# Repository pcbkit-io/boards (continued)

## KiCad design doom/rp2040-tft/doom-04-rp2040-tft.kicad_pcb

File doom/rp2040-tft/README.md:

# 04 · rp2040-tft — the bare RP2040 with a colour screen and an SD card

Variant 02's processor without the module: the RP2040 chip with Raspberry Pi's minimal design
(12 MHz crystal, 16 MB W25Q128 QSPI flash, BOOTSEL and RESET buttons), a 1.8" colour TFT, a
microSD slot for the WAD, PWM sound through a class-D amplifier, and two 18650 Li-ion cells it
charges from its own USB-C. JLCPCB assembles everything but the display module, which plugs into
the socket it solders.

| | |
|---|---|
| Processor | RP2040 (QFN-56): 2 × **Cortex-M0+** (ARMv6-M), 133 MHz rated (rp2040-doom: 270 MHz), 264 KB SRAM, no internal flash; W25Q128JVSIQ 16 MB on the QSPI (XIP), 12 MHz crystal |
| Display | 1.8" 128 × 160 TFT, ST7735S (MSP1803), SPI0 (GPIO18 SCK, GPIO19 MOSI, GPIO17 CS, GPIO20 A0/DC, GPIO21 RESET), backlight GPIO22 |
| Storage | microSD (Hirose DM3AT) on SPI1 (GPIO10–13), card detect GPIO14 |
| Input | 8 × 6 mm tact switches: GPIO2–GPIO9 |
| Sound | GPIO15 PWM → 1 kΩ / 10 nF low-pass → PAM8403 (left channel, shutdown on GPIO16) → 8 Ω speaker on JST PH |
| Power | 2 × 18650 Li-ion in parallel (1S2P, a 2 A resettable fuse per cell) → reverse-cell P-FET (AO3401A) → DW01A + FS8205A protection; BQ24075 charger with power path from USB-C (1 A PTC + TVS on VBUS); its SYS output feeds the TLV75533 3.3 V LDO (enabled by the slide switch) and the PAM8403 |
| Programming | USB-C to the RP2040's USB (27 Ω series, USBLC6 ESD array): hold BOOT, tap RESET → the boot ROM's UF2 drive; SWD on a 3-pin header on the back |
| Board | 132 × 104 mm, **4 layers** (GND plane on In1), four M3 holes; front: display, buttons, BOOT, RESET, on/off switch, USB-C, charge LEDs, test pads; back: the RP2040 and the rest, the two 18650 holders across the top half |

<!-- STATUS -->
**Board status** (measured on the dev host with PCBKit's CLI): `pcbkit check`: complete — 0 errors, 4 warnings (diff-pair-uncoupled, erc-rail-name, track-width-class), 0 unrouted nets. 94 components, 71 nets, 973 track segments (2561 mm), 124 vias.
`analysis.run { lens: "ready" }`: Typical scenario, partly by family estimates. Nothing to fix, 4 to consider, 16 ok: weigh the warnings (tell the person about the ones that are their choice), then the board is ready to order.
`pcbkit export --format fab` succeeds without `--force`: every assembled line of the BOM has an LCSC code.

| Warning | Why it stays |
|---|---|
| `diff-pair-uncoupled`, `skew` (CONN_DP / CONN_DN, ~48 mm) | USB full speed (12 Mbit/s): the connector is on the front edge, the RP2040 on the back; tens of mm uncoupled and a millimetre of skew are harmless against 4–20 ns edges |
| `track-width-class` (CONN_DP / CONN_DN necked to 0.15–0.19 mm) | short necks at the 0.4 mm pitch pads of the QFN-56 and the USB-C; signals only |
| ready lens: thermal parameters, typical scenario | estimates of the analysis, not faults of the board |
<!-- /STATUS -->

## Run it in the browser

Open https://app.pcbkit.io/github/pcbkit-io/boards/tree/main/doom/rp2040-tft, open the
Laboratory and press **Build & run**: the page builds `doom/` for the RP2040's Cortex-M0+ (with
rp2040-doom's `DOOM1.WHX` linked into the flash), boots it the way the chip's boot ROM does (the
boot2 stage checked by its CRC, then the flash in place), and draws the ST7735's frames on the
board. Play with the keyboard (arrows, F fire, Space use, M menu, Enter) or a gamepad
(`input.js`).

## Why it runs Doom

`doom/` is rp2040-doom's engine (kilograham, GPL-2, its compressed level format and its
`DOOM1.WHX`) on PCBKit's RP2040 kit instead of the Pico SDK: one core at 200 MHz (the core voltage
raised to 1.15 V first, as the SDK does above 133 MHz), the WAD read in place from the 16 MB flash,
the zone heap in the SRAM. Each 320 × 200 frame is halved (2 × 2 blocks averaged) into the panel's
middle 160 × 100, landscape, RGB565 over SPI0 at 15 MHz: 32 KB per frame, ~17 ms. The eight buttons
are read from GPIO2–9 (pulled up). The firmware does not use the microSD slot or the speaker yet:
the WAD is in the flash and the game is silent.

## Power

Two 18650 Li-ion cells in Keystone 1042 holders on the back, in parallel (1S2P, 3.0–4.2 V, about
5–7 Ah together), as on `rp2350-handheld`:

- **Reverse cells:** an AO3401A P-MOSFET in the plus line, its gate at the cells' minus: cells put
  in backwards leave it off and the board unpowered (it conducts both ways when they are right, so
  charging goes through it too). One cell reversed against the other is what the **per-cell fuses**
  are for: each holder's + reaches the pack through its own 2 A resettable fuse (Littelfuse
  1812L200/16GR: 16 V, 100 A interrupting), so a cell put in backwards, or one much fuller than
  the other, trips both in milliseconds instead of shorting the two cells together (tens of
  amperes); take the cell out and they reset. Still put each cell's + at the end the silkscreen
  marks.
- **Protection:** DW01A + FS8205A in the pack's minus: over-charge 4.3 V, over-discharge 2.4 V,
  over-current about 3 A and short circuit, for the pack. Flat-top unprotected 18650 cells fit
  the holders.
- **Charger with power path:** a TI BQ24075 from the USB-C VBUS (through a 1 A PTC fuse, a 5 V TVS
  after it), in USB500 mode (at most 500 mA from the port; the CC pins' 5.1 kΩ make any Type-C
  source give 5 V), 800 mA fast charge (RISET 1.13 kΩ), input limit RILIM 1.18 kΩ, safety timers
  off (two cells charge longer than its longest timer; termination is by current), TS tied to
  10 kΩ (no thermistor). Its output SYS runs the board from USB when one is plugged in and from
  the cells otherwise.
- **Rails:** SYS (3.0–5.5 V) feeds the TLV75533 LDO (3.3 V, 500 mA; it follows the cells below about
  3.55 V, where the RP2040, the flash, the card and the display still run) and the PAM8403 directly.
  The slide switch on the left edge enables the LDO (100 kΩ holds it off); a 100 kΩ pull-down keeps
  the amplifier shut down while the RP2040 is off. The cells keep charging with the switch off.

| State | Current (estimate) |
|---|---|
| RP2040 at 270 MHz, both cores | ~50 mA |
| ST7735 with backlight | ~25 mA |
| SD card reading (bursts) | 20–60 mA |
| PAM8403 at moderate volume | 30–100 mA from SYS |
| **Typical** | **~100 mA at 3.7 V** |

Two 3000 mAh cells → **about 55 h** of play (estimate). A full charge of two empty cells at 800 mA
takes about 8 h (longer from a 500 mA USB 2.0 port).

## Charging

Plug a USB-C charger or computer into the USB-C on the bottom edge. The red LED (CHG) is on while
the cells charge and goes out when they are full; the green LED (USB) is on while USB power is
present. The board runs from USB while it charges, switched on or off. Insert both cells with +
at the end the back's silkscreen marks.

## Modules plugged in by hand

- **DS1: 1.8" 128 × 160 ST7735S SPI TFT module** (MSP1803 pinout, 8 pins: VCC, GND, CS, RESET,
  A0, SDA, SCK, LED) into the 1x8 socket JLCPCB solders on the front.
- An **8 Ω speaker** (0.5–2 W) with a JST PH 2-pin plug into J5 at the right edge of the back.
- Two **18650 cells** (the microSD card is optional: the firmware does not read it yet).

## Firmware: build and flash

- **Build:** in PCBKit, the Laboratory's **Build & run** builds `doom/` (Cortex-M0+, the kit's
  boot2 for the W25Q128 and its start-up); then export the firmware
  (`export.run { format: "firmware" }`): `U1.uf2`, the program and the WAD.
- **Flashing on arrival:** nothing to solder and no programmer, the RP2040's boot ROM has a USB
  loader. Connect the USB-C to a computer, hold **BOOT**, tap **RESET**, release BOOT (or hold BOOT
  while plugging in): the board appears as the **RPI-RP2** drive. Copy `U1.uf2` onto it; the
  RP2040 writes it into the W25Q128 and restarts into Doom. Or over SWD: the 3-pin header on the
  back (SWCLK, GND, SWDIO) takes a Raspberry Pi Debug Probe.

## Bill of materials

Rough cost at 10 pieces (estimates): RP2040 $0.80 · W25Q128 $1.00 · crystal $0.30 · ST7735 module
$3.00 · microSD socket $0.60 · PAM8403 $0.15 · BQ24075 $1.10 · DW01A + FS8205A + AO3401A $0.25 ·
TLV75533 $0.20 · USB-C + ESD + TVS + PTC $0.50 · buttons $3.00 · passives $1.00 · two 18650 holders
$9.80 · 4-layer PCB $3.00 · speaker $1.00 → **about $26** without the cells, plus assembly.

<!-- BOM -->
The assembly BOM as `pcbkit export --format fab` writes it (JLCPCB assembly: LCSC codes; the modules' lines are their sockets):

| Qty | Refs | Part | LCSC | Footprint |
|---|---|---|---|---|
| 2 | BT1, BT2 | 1042 | C5249310 | BatteryHolder_Keystone_1042_1x18650 |
| 12 | C1, C2, C3, C4, C5, C9, C12, C13, C14, C15, C18, C19 | 100nF | C1525 | C_0402_1005Metric |
| 1 | C6 | 10uF | C19702 | C_0603_1608Metric |
| 1 | C7 | 10nF | C15195 | C_0402_1005Metric |
| 6 | C10, C11, C24, C25, C26, C28 | 1uF | C52923 | C_0402_1005Metric |
| 2 | C16, C17 | 15pF | C1548 | C_0402_1005Metric |
| 3 | C22, C23, cIn | 1uF | C15849 | C_0603_1608Metric |
| 1 | C27 | 22uF | C12891 | C_1206_3216Metric |
| 1 | C29 | 470nF | C47339 | C_0402_1005Metric |
| 1 | D1 | tvs 5V | C918844 | D_SOD-323 |
| 1 | DS1 | MSP1803 1.8in 128x160 SPI TFT module (ST7735S) | C2905417 | TFT_1.8in_ST7735_Socket_1x08_P2.54mm |
| 1 | F1 | PTC 750mA | C20800 | Fuse_1206_3216Metric |
| 2 | F2, F3 | PTC 2000mA | C18198340 | Fuse_1812_4532Metric |
| 1 | J1 | USB4105-GF-A | C165948 | USB_C_Receptacle_USB2.0_16P |
| 1 | J3 | PinHeader_1x03_P2.54mm_Vertical | C49257 | PinHeader_1x03_P2.54mm_Vertical |
| 1 | J4 | DM3AT-SF-PEJM5 | C114218 | Hirose_DM3AT_microSD_socket_push-push |
| 1 | J5 | S2B-PH-K-S(LF)(SN) | C173752 | JST_PH_S2B-PH-K_1x02_P2.00mm_Horizontal |
| 1 | Q1 | AO3401A | C15127 | SOT-23 |
| 1 | Q2 | FS8205A | C5148694 | TSSOP-8_4.4x2.93mm_P0.65mm |
| 4 | R1, R10, R17, rBoot | 1kohm | C11702 | R_0402_1005Metric |
| 2 | R2, R3 | 27ohm | C25100 | R_0402_1005Metric |
| 6 | R4, R6, R7, R8, R9, rTs | 10kohm | C25744 | R_0402_1005Metric |
| 3 | R11, R12, R15 | 100kohm | C25741 | R_0402_1005Metric |
| 2 | R13, R14 | 5.1kohm | C25905 | R_0402_1005Metric |
| 1 | R16 | 100ohm | C25076 | R_0402_1005Metric |
| 10 | SW1, SW2, SW3, SW4, SW5, SW6, SW7, SW8, boot, reset | PTS645SM43SMTR92 LFS | C221880 | SW_Tactile_SPST_6x6mm_SMD |
| 1 | SW9 | MSK12C02 | C431540 | SW_Slide_SPDT_Shouhan_MSK12C02 |
| 1 | U1 | RP2040 | C2040 | QFN-56-1EP_7x7mm_P0.4mm_EP3.1x3.1mm |
| 1 | U2 | DW01A | C351410 | SOT-6_1.6x2.9mm_P0.95mm |
| 1 | U3 | W25Q128JVSIQ | C97521 | SOIC-8_5.23x5.28mm_P1.27mm |
| 1 | U4 | TLV75533PDBVR | C404027 | SOT-23-5 |
| 1 | U5 | PAM8403DR | C5122557 | SOIC-16_3.9x9.9mm_P1.27mm |
| 1 | U6 | BQ24075RGTR | C15464 | QFN-16-1EP_3x3mm_P0.5mm_EP1.68x1.68mm |
| 1 | U7 | USBLC6-2SC6 | C7519 | SOT-23-6 |
| 1 | Y1 | 12MHz 10pF | C20625731 | Crystal_SMD_3225-4Pin |
| 2 | cBat, cSys | 4.7uF | C1779 | C_0805_2012Metric |
| 1 | ledChg | red | C2286 | LED_0603_1608Metric |
| 1 | ledPg | green | C12624 | LED_0603_1608Metric |
| 2 | rChg, rPg | 1.5kohm | C25867 | R_0402_1005Metric |
| 1 | rIlim | 1.18kohm | C270651 | R_0402_1005Metric |
| 1 | rIset | 1.13kohm | C67014 | R_0402_1005Metric |
<!-- /BOM -->

## What PCBKit's engine must model to simulate it faithfully

Everything of variant 02, plus: the boot ROM's **USB mass-storage UF2 loader** if flashing is to be
simulated; the **SSI/XIP with 16 MB** (the current SoC maps 2 MB); **two PL022 SPI** blocks with
**DMA** (paced by the SPI's DREQ); the **PWM slice** as an audio source (duty → sample); an SD card
model in SPI mode (CMD0/8/55/41/58/17/18/24, a FAT image as its contents); an ST7735 model; the
BQ24075/DW01A/LDO power chain as a two-cell battery model with protection thresholds, the power
path and the charge current.

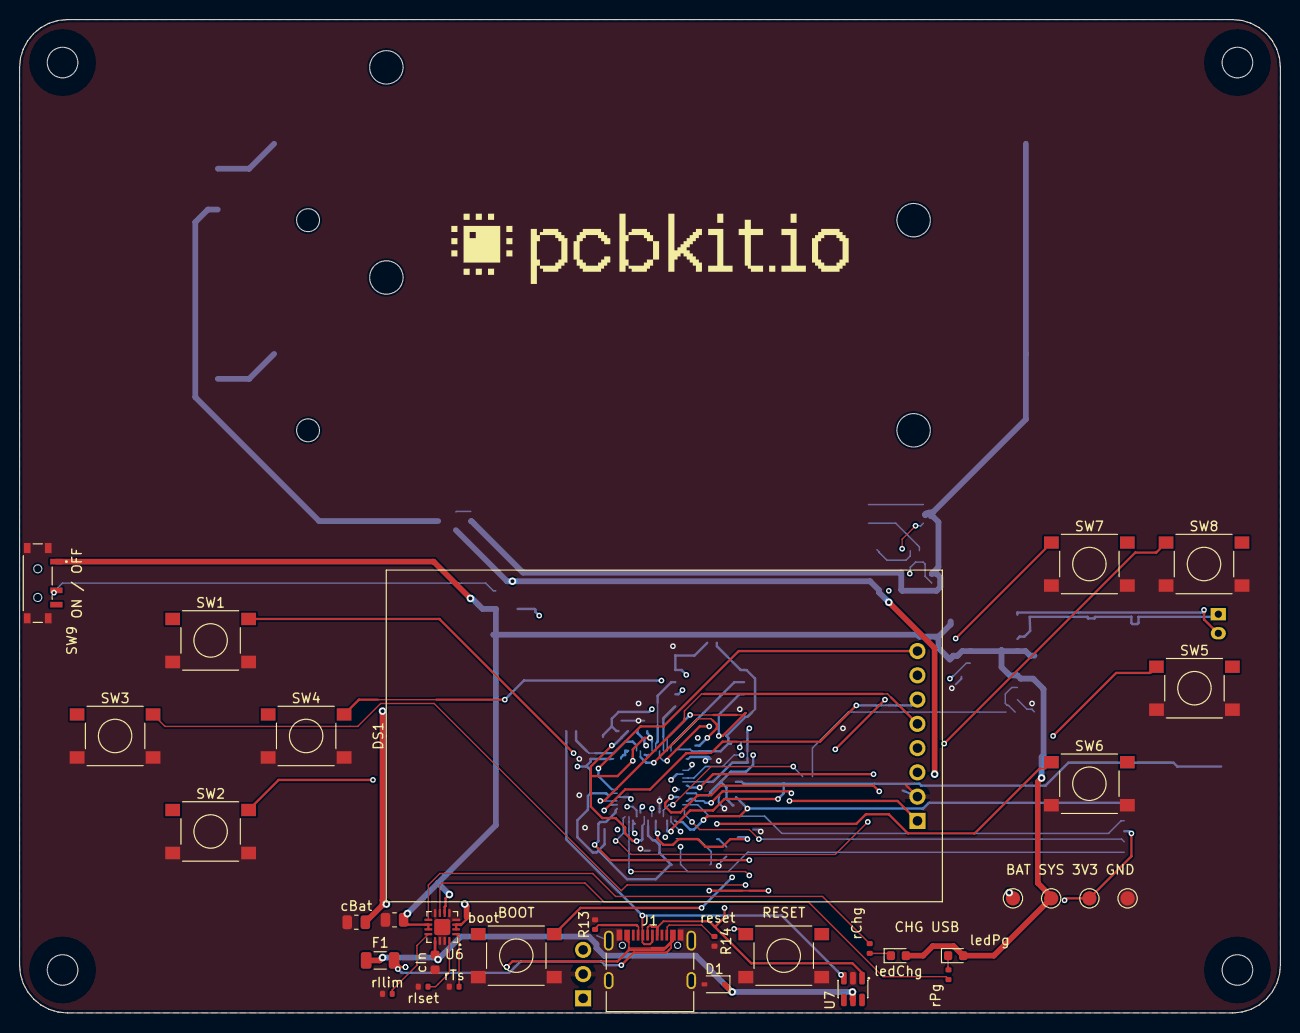
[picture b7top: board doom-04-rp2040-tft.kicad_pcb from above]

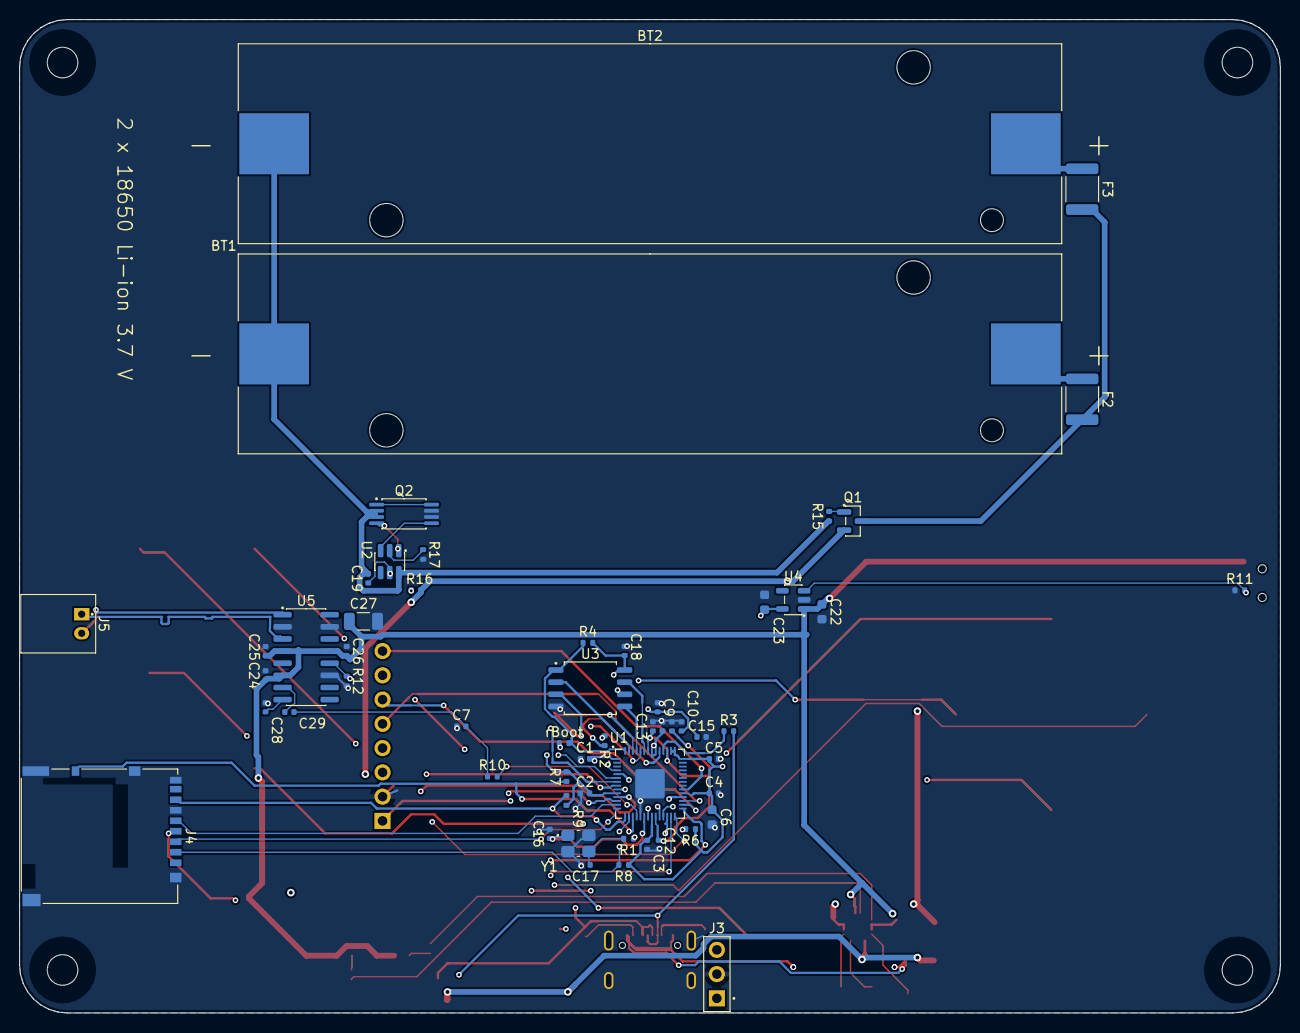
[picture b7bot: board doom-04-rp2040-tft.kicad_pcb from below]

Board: 4 copper layers, 132.0 x 104.0 mm, 94 parts (56 on the bottom side), 70 nets.

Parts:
BT1, BT2: 1042; BatteryHolder_Keystone_1042_1x18650
C1, C2, C3, C4, C5, C9, C12, C13, C14, C15, C18, C19: 100nF; C_0402_1005Metric
C6: 10uF; C_0603_1608Metric
C7: 10nF; C_0402_1005Metric
C10, C11, C24, C25, C26, C28: 1uF; C_0402_1005Metric
C16, C17: 15pF; C_0402_1005Metric
C22, C23: 1uF; C_0603_1608Metric
C27: 22uF; C_1206_3216Metric
C29: 470nF; C_0402_1005Metric
D1: tvs 5V; D_SOD-323
DS1: MSP1803 1.8in 128x160 SPI TFT module (ST7735S); TFT_1.8in_ST7735_Socket_1x08_P2.54mm
F1: PTC 750mA; Fuse_1206_3216Metric
F2, F3: PTC 2000mA; Fuse_1812_4532Metric
H1, H2, H3, H4: MountingHole_3.2mm_M3
J1: USB4105-GF-A; USB_C_Receptacle_USB2.0_16P
J3: PinHeader_1x03_P2.54mm_Vertical
J4: DM3AT-SF-PEJM5; Hirose_DM3AT_microSD_socket_push-push
J5: S2B-PH-K-S(LF)(SN); JST_PH_S2B-PH-K_1x02_P2.00mm_Horizontal
Q1: AO3401A; SOT-23
Q2: FS8205A; TSSOP-8_4.4x2.93mm_P0.65mm
R1, R10, R17: 1kohm; R_0402_1005Metric
R2, R3: 27ohm; R_0402_1005Metric
R4, R6, R7, R8, R9: 10kohm; R_0402_1005Metric
R11, R12, R15: 100kohm; R_0402_1005Metric
R13, R14: 5.1kohm; R_0402_1005Metric
R16: 100ohm; R_0402_1005Metric
SW1, SW2, SW3, SW4, SW5, SW6, SW7, SW8: PTS645SM43SMTR92 LFS; SW_Tactile_SPST_6x6mm_SMD
SW9: MSK12C02; SW_Slide_SPDT_Shouhan_MSK12C02
U1: RP2040; QFN-56-1EP_7x7mm_P0.4mm_EP3.1x3.1mm
U2: DW01A; SOT-6_1.6x2.9mm_P0.95mm
U3: W25Q128JVSIQ; SOIC-8_5.23x5.28mm_P1.27mm
U4: TLV75533PDBVR; SOT-23-5
U5: PAM8403DR; SOIC-16_3.9x9.9mm_P1.27mm
U6: BQ24075RGTR; QFN-16-1EP_3x3mm_P0.5mm_EP1.68x1.68mm
U7: USBLC6-2SC6; SOT-23-6
Y1: 12MHz 10pF; Crystal_SMD_3225-4Pin
boot: PTS645SM43SMTR92 LFS; SW_Tactile_SPST_6x6mm_SMD
cBat: 4.7uF; C_0805_2012Metric
cIn: 1uF; C_0603_1608Metric
cSys: 4.7uF; C_0805_2012Metric
ledChg: red; LED_0603_1608Metric
ledPg: green; LED_0603_1608Metric
logo: Logo_PCBKit_pcbkit.io
rBoot: 1kohm; R_0402_1005Metric
rChg: 1.5kohm; R_0402_1005Metric
rIlim: 1.18kohm; R_0402_1005Metric
rIset: 1.13kohm; R_0402_1005Metric
rPg: 1.5kohm; R_0402_1005Metric
rTs: 10kohm; R_0402_1005Metric
reset: PTS645SM43SMTR92 LFS; SW_Tactile_SPST_6x6mm_SMD
tpBat: TestPoint_Round_D1.5mm
tpGnd: TestPoint_Round_D1.5mm
tpSys: TestPoint_Round_D1.5mm
tpV3: TestPoint_Round_D1.5mm

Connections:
AMP_SD: R12.1 (a), U1.27 (GPIO16), U5.12 (SHDN)
AUDIO: C7.1 (a), C29.1 (a), R10.2 (b)
BAT: Q1.2 (S), R16.1 (a), U6.2 (BAT), U6.3 (BAT), cBat.1 (a), tpBat.1
BAT_IN: F2.2 (b), F3.2 (b), Q1.3 (D)
BOOTSEL: boot.1 (a), rBoot.1 (a)
CELL1_P: BT1.2 (C2), F2.1 (a)
CELL2_P: BT2.2 (C2), F3.1 (a)
CELL_N: BT1.1 (C1), BT2.1 (C1), C19.2 (b), Q2.2 (S1), Q2.3 (S1), R15.1 (a), U2.6 (GND)
CHG_LED: ledChg.1 (K), rChg.1 (a)
CHG_N: U6.9 (nCHG), rChg.2 (b)
CONN_DN: J1.A7 (DN), J1.B7 (DN), R3.2 (b), U7.3 (IO2)
CONN_DP: J1.A6 (DP), J1.B6 (DP), R2.2 (b), U7.1 (IO1)
DOWN: SW2.1 (a), U1.5 (GPIO3)
DVDD: C11.1 (a), C12.1 (a), C13.1 (a), U1.23 (DVDD), U1.45 (VREG_VOUT), U1.50 (DVDD)
FIRE: SW5.1 (a), U1.8 (GPIO6)
GND: C1.2 (b), C2.2 (b), C3.2 (b), C4.2 (b), C5.2 (b), C6.2 (b), C7.2 (b), C9.2 (b), C10.2 (b), C11.2 (b), C12.2 (b), C13.2 (b), C14.2 (b), C15.2 (b), C16.2 (b), C17.2 (b), C18.2 (b), C22.2 (b), C23.2 (b), C24.2 (b), C25.2 (b), C26.2 (b), C27.2 (b), C28.2 (b), D1.2 (A), DS1.2 (GND), J1.A1 (GND), J1.A12, J1.B1 (GND), J1.B12, J1.S1 (SHIELD), J3.2, J4.6 (VSS), J4.10 (CD_B), J4.SH, Q2.6 (S2), Q2.7 (S2), R11.2 (b), R12.2 (b), R13.2 (b), R14.2 (b), R17.2 (b), SW1.2 (b), SW2.2 (b), SW3.2 (b), SW4.2 (b), SW5.2 (b), SW6.2 (b), SW7.2 (b), SW8.2 (b), SW9.4 (SHELL), U1.19 (TESTEN), U1.57 (GND), U3.4 (GND), U4.2 (GND), U5.2 (PGND), U5.11 (GND), U5.15 (PGND), U6.4 (nCE), U6.5 (EN2), U6.8 (VSS), U6.14 (TMR), U6.15 (SYSOFF), U6.17 (VSS), U7.2 (GND), Y1.2 (GND), Y1.4 (GND), boot.2 (b), cBat.2 (b), cIn.2 (b), cSys.2 (b), rIlim.2 (b), rIset.2 (b), rTs.2 (b), reset.2 (b), tpGnd.1
ILIM: U6.12 (ILIM), rIlim.1 (a)
ISET: U6.16 (ISET), rIset.1 (a)
LCD_BL: DS1.8 (LED), U1.34 (GPIO22)
LCD_CS: DS1.3 (CS), U1.28 (GPIO17)
LCD_DC: DS1.5 (A0), U1.31 (GPIO20)
LCD_RST: DS1.4 (RESET), U1.32 (GPIO21)
LDO_EN: R11.1 (a), SW9.2 (COM), U4.3 (EN)
LEFT: SW3.1 (a), U1.6 (GPIO4)
MOSI: DS1.6 (SDA), U1.30 (GPIO19)
unnamed: C16.1 (a), U1.20 (XIN), Y1.1 (X1)
unnamed: C19.1 (a), R16.2 (b), U2.5 (VCC)
unnamed: C28.1 (a), U5.8 (VREF)
unnamed: C29.2 (b), U5.7 (INL)
unnamed: Q2.4 (G1), U2.1 (OD)
unnamed: Q2.5 (G2), U2.3 (OC)
unnamed: R1.1 (a), U1.21 (XOUT)
unnamed: R2.1 (a), U1.47 (USB_DP)
unnamed: R3.1 (a), U1.46 (USB_DM)
unnamed: R4.1 (a), U1.56 (QSPI_SS), U3.1 (nCS), rBoot.2 (b)
unnamed: R17.1 (a), U2.2 (CS)
unnamed: U1.51 (QSPI_SD3), U3.7 (nHOLD)
unnamed: U1.52 (QSPI_SCLK), U3.6 (CLK)
unnamed: U1.53 (QSPI_SD0), U3.5 (DI)
unnamed: U1.54 (QSPI_SD2), U3.3 (nWP)
unnamed: U1.55 (QSPI_SD1), U3.2 (DO)
PG_LED: ledPg.1 (K), rPg.1 (a)
PG_N: U6.7 (nPGOOD), rPg.2 (b)
PWM_L: R10.1 (a), U1.18 (GPIO15)
RIGHT: SW4.1 (a), U1.7 (GPIO5)
RUN: R6.2 (b), U1.26 (RUN), reset.1 (a)
SCK: DS1.7 (SCK), U1.29 (GPIO18)
SD_CD: J4.9 (CD_A), R7.1 (a), U1.17 (GPIO14)
SD_CS: J4.2 (CD_DAT3), R8.2 (b), U1.16 (GPIO13)
SD_MISO: J4.7 (DAT0), R9.2 (b), U1.15 (GPIO12)
SD_MOSI: J4.3 (CMD), U1.14 (GPIO11)
SD_SCK: J4.5 (CLK), U1.13 (GPIO10)
SELECT: SW7.1 (a), U1.12 (GPIO9)
SPK_N: J5.1 (C1), U5.3 (OUTLN)
SPK_P: J5.2 (C2), U5.1 (OUTLP)
START: SW8.1 (a), U1.11 (GPIO8)
SWCLK: J3.1, U1.24 (SWCLK)
SWDIO: J3.3, U1.25 (SWDIO)
SYS: C22.1 (a), C24.1 (a), C25.1 (a), C26.1 (a), C27.1 (a), SW9.1 (A), U4.1 (IN), U5.4 (PVDD), U5.6 (VDD), U5.13 (PVDD), U6.6 (EN1), U6.10 (OUT), U6.11 (OUT), cSys.1 (a), ledChg.2 (A), ledPg.2 (A), tpSys.1
TS: U6.1 (TS), rTs.1 (a)
U1Support/XO: C17.1 (a), R1.2 (b), Y1.3 (X2)
U2Support/DRAIN: Q2.1 (D12), Q2.8 (D12)
UP: SW1.1 (a), U1.4 (GPIO2)
USE: SW6.1 (a), U1.9 (GPIO7)
V3: C1.1 (a), C2.1 (a), C3.1 (a), C4.1 (a), C5.1 (a), C6.1 (a), C9.1 (a), C10.1 (a), C14.1 (a), C15.1 (a), C18.1 (a), C23.1 (a), DS1.1 (VCC), J4.4 (VDD), R4.2 (b), R6.1 (a), R7.2 (b), R8.1 (a), R9.1 (a), U1.1 (IOVDD), U1.10 (IOVDD), U1.22 (IOVDD), U1.33 (IOVDD), U1.42 (IOVDD), U1.43 (ADC_AVDD), U1.44 (VREG_VIN), U1.48 (USB_VDD), U1.49 (IOVDD), U3.8 (VCC), U4.5 (OUT), tpV3.1
VBUS: D1.1 (K), F1.2 (b), U6.13 (IN), U7.5 (VBUS), cIn.1 (a)
reversed/gate: Q1.1 (G), R15.2 (b)
usb/power/cc1: J1.A5 (CC1), R13.1 (a)
usb/power/cc2: J1.B5 (CC2), R14.1 (a)
usb/power/vbusIn: F1.1 (a), J1.A4 (VBUS), J1.A9, J1.B4 (VBUS), J1.B9

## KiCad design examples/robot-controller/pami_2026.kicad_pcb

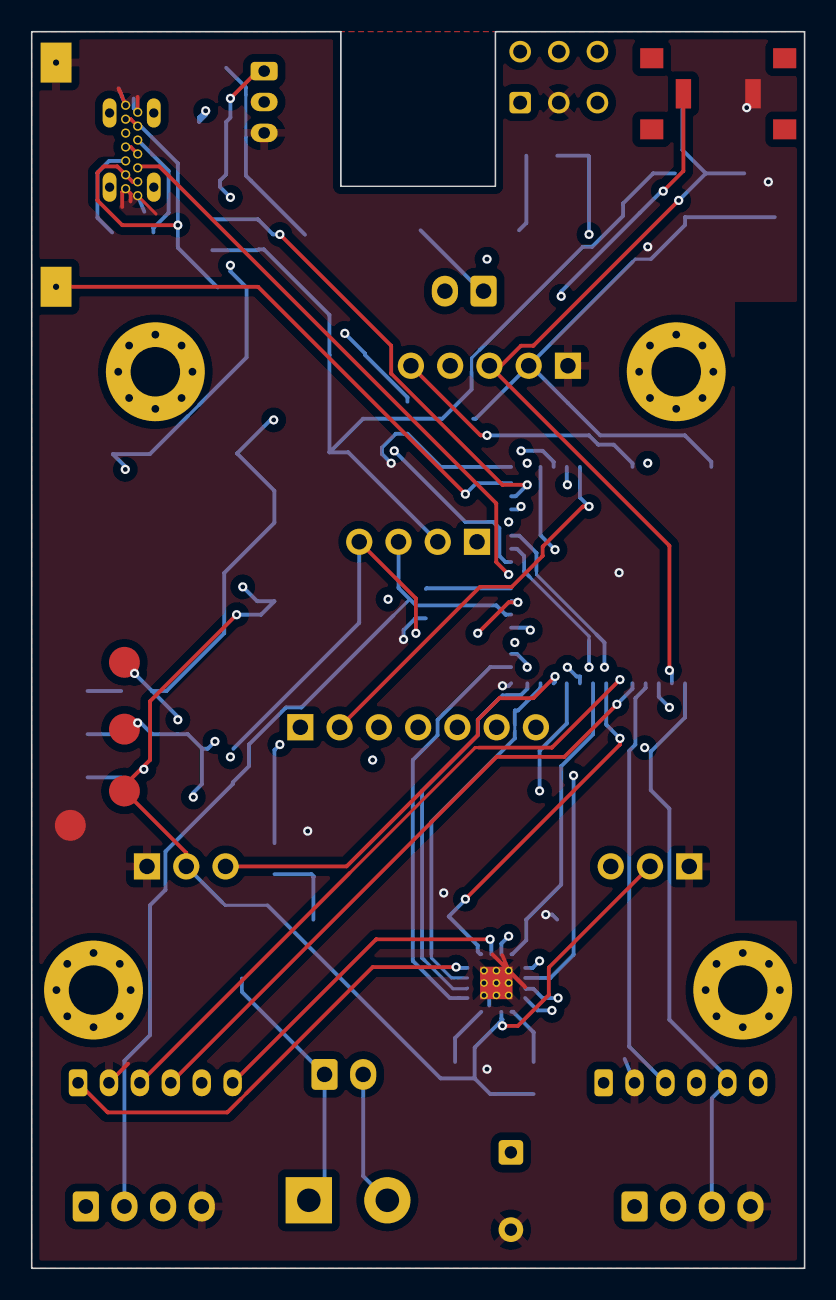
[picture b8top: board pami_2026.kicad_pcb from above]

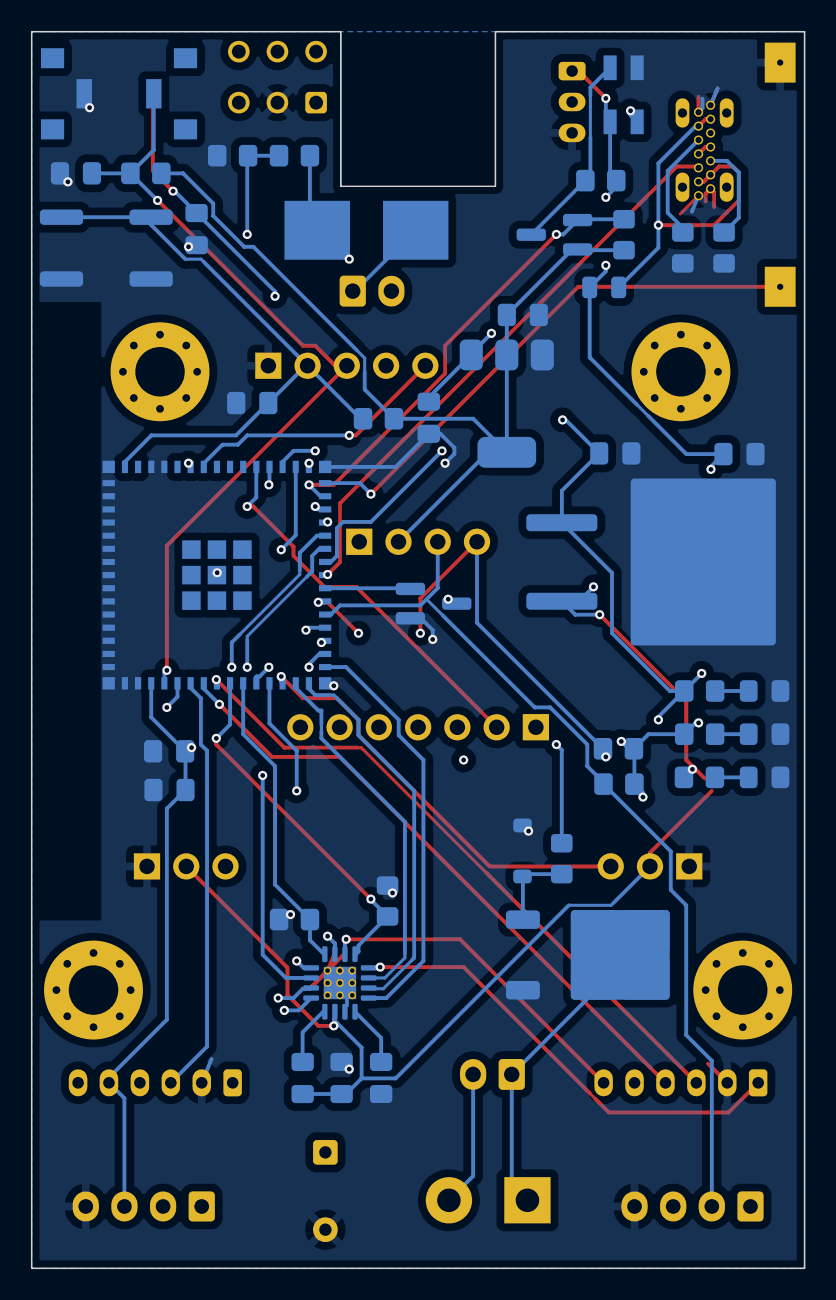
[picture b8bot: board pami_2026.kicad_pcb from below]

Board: 4 copper layers, 50.0 x 80.0 mm, 70 parts (45 on the bottom side), 58 nets.

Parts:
C1: 2.2u; C_0805_2012Metric_Pad1.18x1.45mm_HandSolder
C2, C10: 10u; C_0805_2012Metric_Pad1.18x1.45mm_HandSolder
C3: 10n; C_0805_2012Metric_Pad1.18x1.45mm_HandSolder
C4, C5, C6, C7, C9, C12, C25: 100n; C_0805_2012Metric_Pad1.18x1.45mm_HandSolder
C11: 330n; C_0805_2012Metric_Pad1.18x1.45mm_HandSolder
C18: 220u; CP_Radial_D8.0mm_P5.00mm
D1: D; D_0805_2012Metric
D2, D3, D4: LED; D_0805_2012Metric_Pad1.15x1.40mm_HandSolder
D5: D_Zener; D_SOD-123
D8: SK6812MINI; IN-PI33TBTPRPGPB
F1: Fuse; Fuseholder_Littelfuse_Nano2_154x
H1, H2, H3, H4: MountingHole; MountingHole_3.2mm_M3_Pad_Via
J1: Conn_01x04_Socket; PinHeader_1x04_P2.54mm_Vertical
J2, J14: Conn_01x03_Pin; PinHeader_1x03_P2.54mm_Vertical
J3, J9: Conn_01x04_Pin; JST_XH_B4B-XH-A_1x04_P2.50mm_Vertical
J4: Conn_01x02_Pin; TerminalBlock_bornier-2_P5.08mm
J5: Conn_01x05_Pin; PinHeader_1x05_P2.54mm_Vertical
J6: Conn_01x02_Pin; JST_XH_B2B-XH-A_1x02_P2.50mm_Vertical
J7: Conn_01x03_Pin; JST_PH_B3B-PH-K_1x03_P2.00mm_Vertical
J8: USB_C_Receptacle_USB2.0_14P; MOLEX_2169890001
J10: Conn_01x07_Socket; PinHeader_1x07_P2.54mm_Vertical
J11, J12: Conn_01x06; JST_PH_B6B-PH-K_1x06_P2.00mm_Vertical
Q1: NMOS; WSF22N06
Q2, Q3: NMOS; SOT-23_Handsoldering_nchannel
R1, R7, R8, R14: R; R_0805_2012Metric_Pad1.20x1.40mm_HandSolder
R2, R6: 0.1; R_0805_2012Metric_Pad1.20x1.40mm_HandSolder
R3, R4: 10k; R_0805_2012Metric_Pad1.20x1.40mm_HandSolder
R5, R16: 56k; R_0805_2012Metric_Pad1.20x1.40mm_HandSolder
R9: 470; R_0805_2012Metric_Pad1.20x1.40mm_HandSolder
R10: 150; R_0805_2012Metric_Pad1.20x1.40mm_HandSolder
R11: 330; R_0805_2012Metric_Pad1.20x1.40mm_HandSolder
R12, R13: 5.1k; R_0805_2012Metric_Pad1.20x1.40mm_HandSolder
R17: 100k; R_0805_2012Metric_Pad1.20x1.40mm_HandSolder
SW1: SW_Push; SW_Push_1P1T_NO_CK_KSC9xxJ
SW2: SW_gliss; SW_CK_JS202011AQN_DPDT_Angled
SW3: SW_Push_Open; JST_XH_B2B-XH-A_1x02_P2.50mm_Vertical
SW4: SW_Reed; SW_REED
SW5, SW6: SW_Push; PTS645VSM19PSMTR92LFS
TP1, TP2, TP3, TP12: TestPoint; TestPoint_Pad_D2.0mm
U1: DRV8833RTY; Texas_RTY_WQFN-16-1EP_4x4mm_P0.65mm_EP2.1x2.1mm_ThermalVias
U2: ESP32-S3-MINI-1; ESP32S3MINI1N8
U3: LD1117S33TR_SOT223; SOT-223-3_TabPin2
U4: L7805; TO-263-2

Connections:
+3.3V: C4.1, C10.1, C25.1, J1.2, J3.3, J9.1, J10.7, J11.5, J12.5, Q3.2, R1.1, R4.1, R7.2, R8.1, R10.2, R14.1, TP2.1, U2.3, U3.2
+5V: C2.2, C3.1, C9.1, C12.1, D1.1, D8.4, J2.2, J7.1, J14.2, R3.1, R11.2, TP3.1, U1.10, U3.3, U4.3
+BATT: C11.1, C18.1, F1.2, R9.2, R17.2, TP1.1, U4.1
EN: C6.1, J5.2, R1.2, SW1.2, U2.45
EN_SCREEN: Q2.2, U2.22
GND: C1.1, C2.1, C4.2, C5.2, C6.2, C7.2, C9.2, C10.2, C11.2, C12.2, C18.2, C25.2, D2.1, D3.1, D4.1, D5.2, D8.2, J2.1, J3.4, J5.1, J7.3, J8.A1, J8.A12, J8.B1, J8.B12, J9.4, J11.2, J12.2, J14.1, Q1.3, Q2.3, R2.1, R6.1, R12.2, R13.2, R16.1, SW1.1, SW2.2, SW4.1, SW5.2, SW6.1, TP12.1, U1.11, U1.17, U2.1, U2.2, U2.42, U2.43, U2.46, U2.47, U2.48, U2.49, U2.50, U2.51, U2.52, U2.53, U2.54, U2.55, U2.56, U2.57, U2.58, U2.59, U2.60, U2.61, U2.62, U2.63, U2.64, U2.65, U3.1, U4.2
GPIO0: C5.1, J5.3, R14.2, SW5.1, U2.4
I2C_scl: J1.3, J9.2, R7.1, U2.20
I2C_sda: J1.4, J9.3, R8.2, U2.21
LEVEL_BATTERY: R16.2, R17.1, U2.19
NEOPIXEL: Q3.3, R4.2, U2.29
unnamed: D1.2, J8.A4, J8.A9, J8.B4, J8.B9
unnamed: D2.2, R9.1
unnamed: D3.2, R10.1
unnamed: D4.2, R11.1
unnamed: D5.1, Q1.2, R5.2
unnamed: D8.3, Q3.1, R3.2
unnamed: D8.1, J7.2
unnamed: J1.1, J10.6, Q2.1
unnamed: J4.1, J6.1, Q1.1
unnamed: J4.2, J6.2, SW3.2
unnamed: J8.A5, R13.1
unnamed: J8.B5, R12.1
unnamed: J11.1, U1.16
unnamed: J11.6, U1.2
unnamed: J12.1, U1.5
unnamed: J12.6, U1.3
unnamed: F1.1, R5.1, SW3.1
unnamed: C3.2, U1.9
unnamed: C1.2, U1.12
RX0: J5.4, U2.40
RX_lidar: J3.1, U2.25
SERVO1: J2.3, U2.13
SERVO2: J14.3, U2.12
TX0: J5.5, U2.39
TX_lidar: J3.2, U2.26
button_user: C7.1, SW6.2, U2.28
motor_a+: U1.14, U2.15
motor_a-: U1.13, U2.16
motor_a_sense: R2.2, U1.1, U2.9
motor_b+: U1.7, U2.17
motor_b-: U1.8, U2.18
motor_b_sense: R6.2, U1.4, U2.10
motor_enable: U1.15, U2.14
motor_enc_a+: J11.3, U2.8
motor_enc_a-: J11.4, U2.7
motor_enc_b+: J12.3, U2.6
motor_enc_b-: J12.4, U2.5
motor_fault: U1.6, U2.11
sw_team: SW2.1, U2.27
sw_tirette: SW4.2, U2.30
tft_cs: J10.2, U2.35
tft_dc: J10.3, U2.33
tft_rst: J10.1, U2.34
tft_scl: J10.4, U2.32
tft_sda: J10.5, U2.31
usb_d+: J8.A6, J8.B6, U2.24
usb_d-: J8.A7, J8.B7, U2.23

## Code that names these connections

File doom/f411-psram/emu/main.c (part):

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 * program (Doom for pcbkit-virt, an ELF file) is in the W25Q128 flash, its 8 MiB RAM is the
 * APS6404L PSRAM, its screen the ST7789 and its GPIO inputs the board's eight buttons.
 *
 *   SPI1 (memories): SCK PA5, MISO PA6, MOSI PA7 at 50 MHz; chip selects PSRAM PA4, flash PB2
 *   SPI2 (display): SCK PB13, MOSI PB15 at 25 MHz; CS PB12, D/C PB14, RESET PB1, backlight PB10
 *   buttons to ground, pulled up: up PA1, down PA2, left PA3, right PB4, fire PB6, use PB7,
 *   strafe PB8, menu PB0 (the guest's GPIO 0…7)
 *
 * Every memory transaction is one cache line, read with fast read (0Bh: a dummy byte) from either
 * chip. Each guest frame (320 × 200, 8-bit) goes to the panel's 320 × 200 window through the
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    spi->CR1 |= SPI_CR1_SPE;
}

#define RAM_CS pcbkit_pin(0, 4)
#define ROM_CS pcbkit_pin(1, 2)
#define LCD_CS pcbkit_pin(1, 12)
#define LCD_DC pcbkit_pin(1, 14)
#define LCD_RESET pcbkit_pin(1, 1)
#define LCD_BACKLIGHT pcbkit_pin(1, 10)

static const uint8_t buttons[8] = {pcbkit_pin(0, 1), pcbkit_pin(0, 2), pcbkit_pin(0, 3), pcbkit_pin(1, 4), pcbkit_pin(1, 6), pcbkit_pin(1, 7), pcbkit_pin(1, 8), pcbkit_pin(1, 0)};
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
void rv_host_read(int flash, uint32_t offset, uint8_t *bytes) { line(flash ? ROM_CS : RAM_CS, 0x0b, offset, 0, bytes); }

void rv_host_write(uint32_t offset, const uint8_t *bytes) { line(RAM_CS, 0x02, offset, bytes, 0); }

uint64_t rv_host_time_us(void) { return pcbkit_time_us(); }

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void rv_host_console(uint8_t byte) { (void)byte; }

static void lcd_command(uint8_t command, const uint8_t *data, uint32_t n) {
    pin_put(LCD_CS, 0);
    pin_put(LCD_DC, 0);
    exchange(SPI2, &command, 1, 0, 0, 0);
    pin_put(LCD_DC, 1);
    if (n) exchange(SPI2, 0, 0, data, 0, n);
    pin_put(LCD_CS, 1);
}

static uint16_t palette565[256];
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    const uint8_t pages[] = {0, 20, 0, (uint8_t)(19 + height)};
    lcd_command(0x2a, columns, 4);
    lcd_command(0x2b, pages, 4);
    pin_put(LCD_CS, 0);
    pin_put(LCD_DC, 0);
    static const uint8_t write = 0x2c;
    exchange(SPI2, &write, 1, 0, 0, 0);
    pin_put(LCD_DC, 1);
    static uint8_t row[320], out[640];
    for (uint32_t y = 0; y < height; y++) {
        rv_read(address + y * stride, row, width);
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        }
        exchange(SPI2, 0, 0, out, 0, 2 * width);
    }
    pin_put(LCD_CS, 1);
}

void rv_host_stop(const char *why, uint32_t code, uint32_t pc) {
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}

static void lcd_start(void) {
    pin_output(LCD_CS, 1);
    pin_output(LCD_DC, 1);
    pin_output(LCD_RESET, 1);
    pin_output(LCD_BACKLIGHT, 0);
    pin_function(pcbkit_pin(1, 13), 5);
    pin_function(pcbkit_pin(1, 15), 5);
    spi_start(SPI2, 25000000);
    /* Hardware reset: low for 10 µs or more, then 120 ms before commands. */
    pin_put(LCD_RESET, 0);
    pcbkit_sleep_until(pcbkit_time_us() + 1000);
    pin_put(LCD_RESET, 1);
    pcbkit_sleep_until(pcbkit_time_us() + 120000);
    /* The IPS panel (normally black) shows true colours only with inversion on; the module lies
     * turned, its header to the left: row/column exchange and column mirror, RGB. */
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    lcd_command(0x2a, all_columns, 4);
    lcd_command(0x2b, all_pages, 4);
    static const uint8_t write = 0x2c, black[64];
    pin_put(LCD_CS, 0);
    pin_put(LCD_DC, 0);
    exchange(SPI2, &write, 1, 0, 0, 0);
    pin_put(LCD_DC, 1);
    for (unsigned i = 0; i < 320 * 240 * 2 / sizeof black; i++) exchange(SPI2, 0, 0, black, 0, sizeof black);
    pin_put(LCD_CS, 1);
    pin_put(LCD_BACKLIGHT, 1);
}

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    clock_start();
    for (unsigned i = 0; i < 8; i++) pin_input(buttons[i], 1);
    if (!pin_get(buttons[7])) for (;;) __asm__ volatile("wfi");
    pin_output(RAM_CS, 1);
    pin_output(ROM_CS, 1);
    pin_function(pcbkit_pin(0, 5), 5);
    pin_function(pcbkit_pin(0, 6), 5);
    pin_function(pcbkit_pin(0, 7), 5);
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    /* The PSRAM's power-up time (150 µs), then its reset. */
    pcbkit_sleep_until(pcbkit_time_us() + 200);
    static const uint8_t reset_enable = 0x66, reset = 0x99;
    pin_put(RAM_CS, 0);
    exchange(SPI1, &reset_enable, 1, 0, 0, 0);
    pin_put(RAM_CS, 1);
    pin_put(RAM_CS, 0);
    exchange(SPI1, &reset, 1, 0, 0, 0);
    pin_put(RAM_CS, 1);
    lcd_start();
    rv_run(8u << 20);
    return 0;
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
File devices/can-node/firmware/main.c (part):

/* The robot sensor node: every 10 ms (TIM6 at 100 Hz) the four pressure inputs (ADC1 IN1-IN4 on
 * PA0-PA3 through their dividers, converted in one sequence into memory by DMA) and the
 * ICM-42688-P's accelerations and rotation rates (I2C1 at 400 kHz) go out on CAN at 500 kbit/s:
 *   0x100  pressures: four 16-bit values, millivolts at the 0-5 V inputs (little-endian)
 *   0x101  acceleration X, Y, Z in mg, then the IMU's temperature in 0.01 °C (16-bit each)
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    HAL_UART_Init(&uart);   /* the console again, at the new clock */
    printf("can-node %lu Hz\n", (unsigned long)HAL_RCC_GetSysClockFreq());

    /* Status LED on PB0. */
    pins(GPIOB, GPIO_PIN_0, GPIO_MODE_OUTPUT_PP, 0);

    /* The four inputs: one sequence, into memory by DMA (DMAMUX request ADC1). */
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    }
    if (HAL_ADCEx_Calibration_Start(&adc, ADC_SINGLE_ENDED) != HAL_OK) fail("adc calibration");

    /* The IMU on I2C1: PA15 SCL, PB7 SDA, 400 kHz at 170 MHz. */
    pins(GPIOA, GPIO_PIN_15, GPIO_MODE_AF_OD, GPIO_AF4_I2C1);
    pins(GPIOB, GPIO_PIN_7, GPIO_MODE_AF_OD, GPIO_AF4_I2C1);
    i2c.Instance = I2C1;
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    if (HAL_I2C_Init(&i2c) != HAL_OK) fail("i2c");
    imu_start();

    /* FDCAN1 on PA11 (RX) / PA12 (TX): classic CAN at 500 kbit/s from PCLK1 (170 MHz / 17, 20 tq);
     * frame 0x200 to FIFO 0, the rest rejected. */
    pins(GPIOA, GPIO_PIN_11 | GPIO_PIN_12, GPIO_MODE_AF_PP, GPIO_AF9_FDCAN1);
    can.Instance = FDCAN1;
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
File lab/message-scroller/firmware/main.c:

/* PCBKit message scroller. Type a line into the serial console (9600 baud): it scrolls across
 * the eight digits of a MAX7219 in a seven-segment font, letters included, a dot joining the
 * character before it. The knob sets the speed. A receive interrupt collects the line and echoes
 * every byte; Enter shows it. The CPU sleeps between interrupts. */
#include <avr/io.h>
#include <avr/interrupt.h>
#include <avr/sleep.h>
#include <stdint.h>

#define LINE 64

static volatile uint16_t ms;
ISR(TIMER0_COMPA_vect) { ms++; }
static uint16_t now(void) { cli(); uint16_t t = ms; sei(); return t; }

/* Received characters until Enter; `ready` says a line is complete. */
static volatile char typed[LINE];
static volatile uint8_t length, ready;
static void send(uint8_t b) { while (!(UCSR0A & (1 << UDRE0))) {} UDR0 = b; }
ISR(USART_RX_vect) {
    uint8_t b = UDR0;
    if (b == '\r') return;
    send(b);
    if (b == '\n') { if (length) ready = 1; return; }
    if (!ready && length < LINE) typed[length++] = b;
}

/* Seven segments for each printable character, from space: bit 7 DP, then A…G. */
static const uint8_t font[] = {
    0x00, 0xa0, 0x22, 0x00, 0x00, 0x00, 0x00, 0x02, 0x4e, 0x78, 0x00, 0x00, 0x80, 0x01, 0x80, 0x25, /*  !"#$%&'()*+,-./ */
    0x7e, 0x30, 0x6d, 0x79, 0x33, 0x5b, 0x5f, 0x70, 0x7f, 0x7b, 0x00, 0x00, 0x0d, 0x09, 0x19, 0xe5, /* 0123456789:;<=>? */
    0x7d, 0x77, 0x1f, 0x4e, 0x3d, 0x4f, 0x47, 0x5e, 0x37, 0x06, 0x3c, 0x57, 0x0e, 0x54, 0x15, 0x7e, /* @ABCDEFGHIJKLMNO */
    0x67, 0x73, 0x05, 0x5b, 0x0f, 0x3e, 0x1c, 0x2a, 0x37, 0x3b, 0x6d, 0x4e, 0x13, 0x78, 0x62, 0x08, /* PQRSTUVWXYZ[\]^_ */
};
static uint8_t glyph(uint8_t c) {
    if (c >= 'a' && c <= 'z') c -= 'a' - 'A';
    return c >= ' ' && c < ' ' + sizeof font ? font[c - ' '] : 0x01;
}

/* The message as segments, eight blanks before and after it so it scrolls in and out. */
static uint8_t shown[8 + LINE + 8], count;
static void compose(const volatile char *text, uint8_t n) {
    count = 0;
    for (uint8_t i = 0; i < 8; i++) shown[count++] = 0;
    for (uint8_t i = 0; i < n; i++) {
        uint8_t c = text[i];
        if ((c == '.' || c == ',') && count > 8 && !(shown[count - 1] & 0x80)) shown[count - 1] |= 0x80;
        else shown[count++] = glyph(c);
    }
    for (uint8_t i = 0; i < 8; i++) shown[count++] = 0;
}

static void spi(uint8_t byte) { SPDR = byte; while (!(SPSR & (1 << SPIF))) {} (void)SPDR; }
static void reg(uint8_t r, uint8_t value) { PORTB &= ~(1 << PB2); spi(r); spi(value); PORTB |= 1 << PB2; }
static uint16_t knob(void) { ADCSRA |= 1 << ADSC; while (ADCSRA & (1 << ADSC)) {} return ADC; }
static void print(const char *s) { while (*s) send(*s++); }

int main(void) {
    DDRB = (1 << PB2) | (1 << PB3) | (1 << PB5); PORTB = 1 << PB2;
    SPCR = (1 << SPE) | (1 << MSTR);
    ADMUX = 1 << REFS0; ADCSRA = (1 << ADEN) | (1 << ADPS2) | (1 << ADPS1) | (1 << ADPS0);
    reg(15, 0); reg(9, 0); reg(11, 7); reg(10, 10); reg(12, 1);
    UBRR0 = F_CPU / 16UL / 9600UL - 1;
    UCSR0C = (1 << UCSZ01) | (1 << UCSZ00);
    UCSR0B = (1 << RXEN0) | (1 << TXEN0) | (1 << RXCIE0);
    OCR0A = 249; TCCR0A = 1 << WGM01; TCCR0B = (1 << CS01) | (1 << CS00); TIMSK0 = 1 << OCIE0A;
    set_sleep_mode(SLEEP_MODE_IDLE); sleep_enable(); sei();
    static const char hello[] = "HELLO FROM PCBKIT. TYPE A MESSAGE AND PRESS ENTER.";
    compose(hello, sizeof hello - 1);
    print("Type a message and press Enter.\n");
    uint8_t at = 0;
    uint16_t last = now();
    for (;;) {
        sleep_cpu();
        if (ready) {
            compose(typed, length);
            cli(); length = 0; ready = 0; sei();
            at = 0;
        }
        /* 60…310 ms per step: the knob up is faster. */
        if ((uint16_t)(now() - last) < 60 + ((1023 - knob()) >> 2)) continue;
        last = now();
        for (uint8_t i = 0; i < 8; i++) reg(8 - i, shown[at + i]);
        if (++at + 8 > count) at = 0;
    }
}
